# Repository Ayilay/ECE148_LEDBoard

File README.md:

# ECE148 LED Board

A PCB that arranges WS2812b individually addressable RGB LEDs in a rectangle underneath a Jetson Nano to give it a swank gaming-PC aesthetic.
Designed for [UCSD's ECE148 final project by Team 1, SP21](https://guitar.ucsd.edu/maeece148/index.php/2021SpringTeam1).

## PCB Overview

This PCB was hastily designed and is not my finest work, due to the time constraint we faced and the
fact that turnaround times for PCBs take a few days unless one pays a small fortune.

The PCB was designed in [KiCad](https://www.kicad.org/).

**Features:**
- STM32 F103C8T6 Microcontroller
- 10-pin SWD debug header
- JST-PH power connector with MIC5219 3V3 LDO Regulator
- Power LED
- Input voltage range from 3.7 V to 5V
- 16x WS2812b (aka Neopixels) arranged in a rectangle

**Absent Features**

I mention these not to roast myself (well kinda), but as a disclaimer to those looking at my design 
as reference for theirs. As I mentioned, I was on a time crunch so I couldn't afford the time to make this
a good-quality PCB. The following features should be included in a good design:
- Reset Pushbutton
- Generic I/O Breakouts
- Generic Button/LED for testing
- Testpoints for signals/power

## Firmware Overview

I used Michael Tien's STM32 code for [driving WS2812B LEDs using SPI over DMA](https://michaeltien8901.github.io/stm32/2018/07/19/Using-STM32-SPI-For-LED-STRIP.html)

Porting his code was easy. I created a new STM32CubeMX project for an STM32F103C8T6 microcontroller,
enabled the SPI1 peripheral, added a DMA channel for it, and set the clock as he described.

Then I automatically generated the code, and copied over Tien's helper functions from his `main.c` file,
and it worked like a charm. His functions are very straightforward to use, so thanks!

## Programming the board

(TODO Pictures)

I dislike using clunky IDEs unless I absolutely have to (i.e. for large projects). So I setup my CubeMX
project to use a Makefile, and use `make` to compile the code. Then I use my STLink V3-SET debug adapter
to flash the code, though any ST-Link probe that has a mini 10-pin cable will do. A quick guide on how
I flash STM32 code is on my [CubeProgrammer TechNotes](https://github.com/Ayilay/dotfiles/blob/master/techNotes/CubeProgrammer.md)

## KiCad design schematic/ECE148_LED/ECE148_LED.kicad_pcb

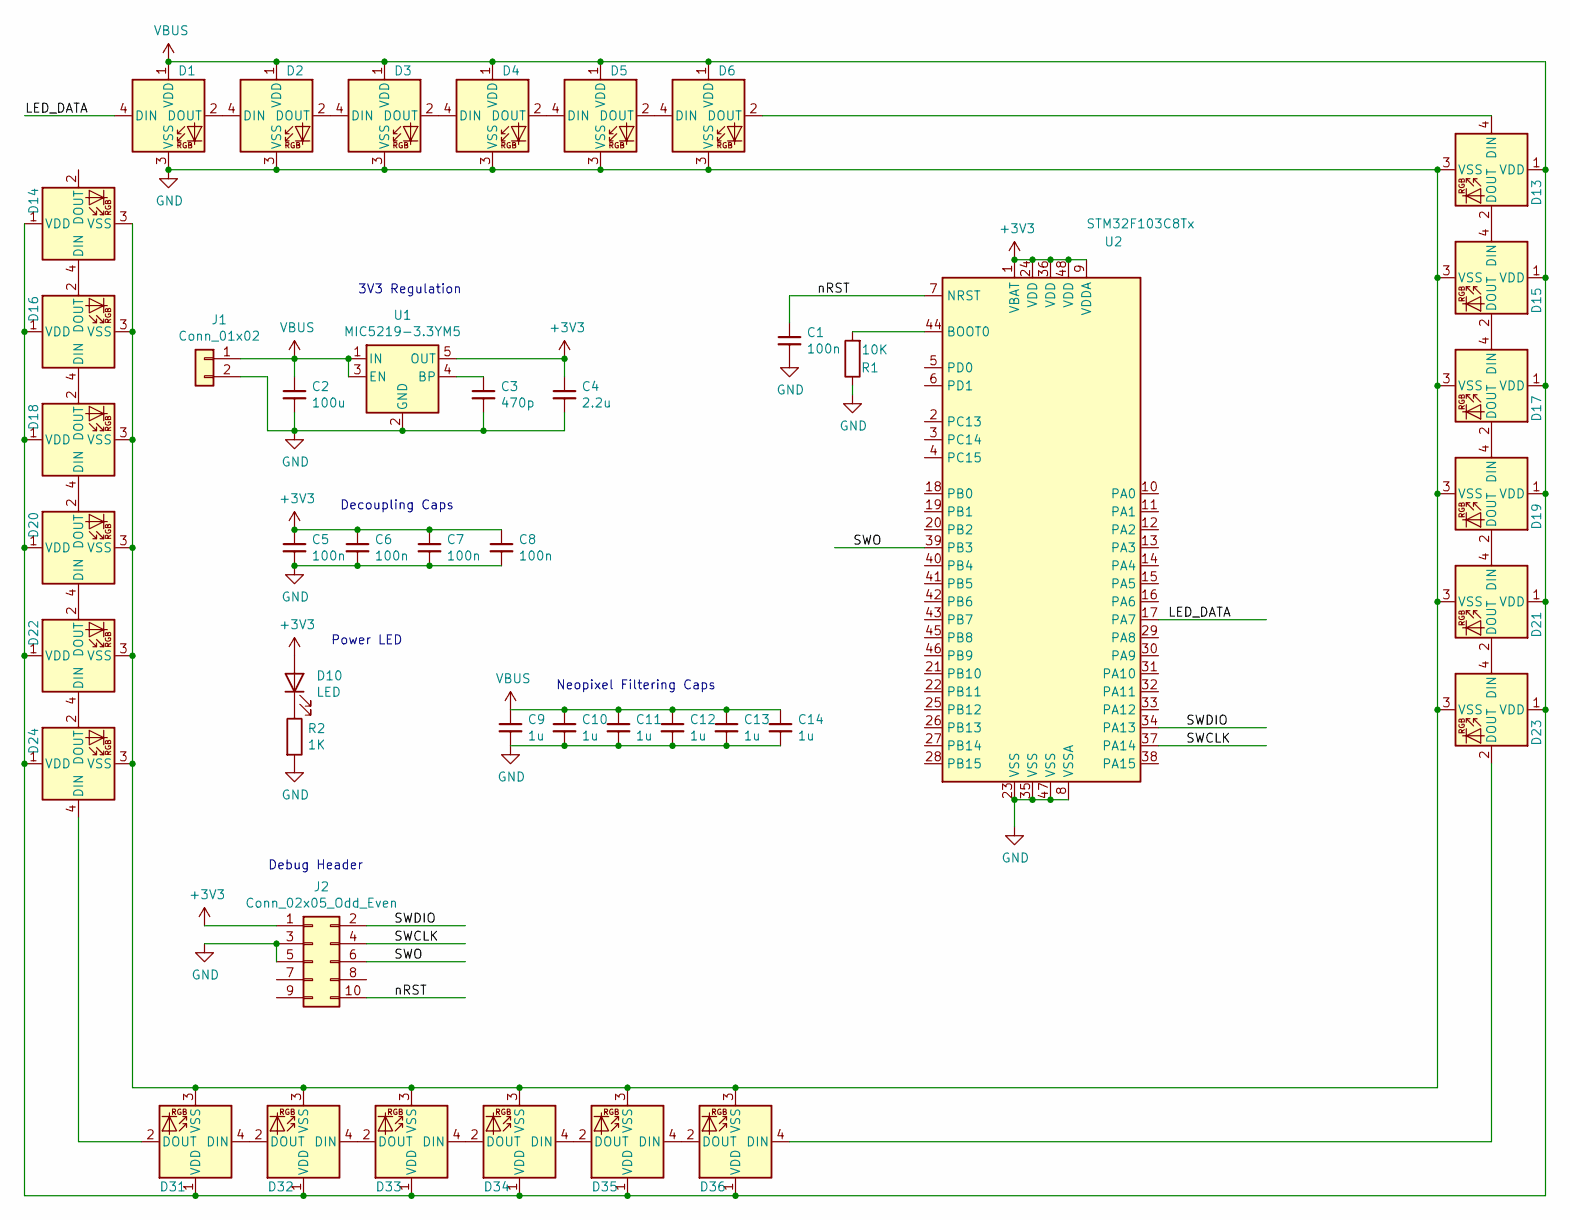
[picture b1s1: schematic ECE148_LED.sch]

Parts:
C1, C5, C6, C7, C8: 100n; C_0603_1608Metric
C2: 100u; CP_Radial_D5.0mm_P2.00mm
C3: 470p; C_0603_1608Metric
C4: 2.2u; C_0603_1608Metric
C9, C10, C11, C12, C13, C14: 1u; C_0603_1608Metric
D1, D2, D3, D4, D5, D6, D13, D14, D15, D16, D17, D18, D19, D20, D21, D22, D23, D24, D31, D32, D33, D34, D35, D36: WS2812B; LED_WS2812B_PLCC4_5.0x5.0mm_P3.2mm
D10: LED; LED_0805_2012Metric
J1: Conn_01x02; JST_PH_B2B-PH-K_1x02_P2.00mm_Vertical
J2: Conn_02x05_Odd_Even; PinHeader_2x05_P1.27mm_Vertical_SMD
R1: 10K; R_0603_1608Metric
R2: 1K; R_0603_1608Metric
U1: MIC5219-3.3YM5; SOT-23-5
U2: STM32F103C8Tx; LQFP-48_7x7mm_P0.5mm

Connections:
+3V3: C4.1, C5.1, C6.1, C7.1, C8.1, D10.2 (A), J2.1, U1.5 (OUT), U2.1 (VBAT), U2.9 (VDDA), U2.24 (VDD), U2.36 (VDD), U2.48 (VDD)
/LED_DATA: D1.4 (DIN), U2.17 (PA7)
/SWCLK: J2.4, U2.37 (PA14)
/SWDIO: J2.2, U2.34 (PA13)
/SWO: J2.6, U2.39 (PB3)
/nRST: C1.1, J2.10, U2.7 (NRST)
GND: C1.2, C2.2, C3.2, C4.2, C5.2, C6.2, C7.2, C8.2, C9.2, C10.2, C11.2, C12.2, C13.2, C14.2, D1.3 (VSS), D2.3 (VSS), D3.3 (VSS), D4.3 (VSS), D5.3 (VSS), D6.3 (VSS), D13.3 (VSS), D14.3 (VSS), D15.3 (VSS), D16.3 (VSS), D17.3 (VSS), D18.3 (VSS), D19.3 (VSS), D20.3 (VSS), D21.3 (VSS), D22.3 (VSS), D23.3 (VSS), D24.3 (VSS), D31.3 (VSS), D32.3 (VSS), D33.3 (VSS), D34.3 (VSS), D35.3 (VSS), D36.3 (VSS), J1.2, J2.3, J2.5, R1.1, R2.2, U1.2 (GND), U2.8 (VSSA), U2.23 (VSS), U2.35 (VSS), U2.47 (VSS)
unnamed: C3.1, U1.4 (BP)
unnamed: D1.2 (DOUT), D2.4 (DIN)
unnamed: D2.2 (DOUT), D3.4 (DIN)
unnamed: D3.2 (DOUT), D4.4 (DIN)
unnamed: D4.2 (DOUT), D5.4 (DIN)
unnamed: D5.2 (DOUT), D6.4 (DIN)
unnamed: D10.1 (K), R2.1
unnamed: D13.2 (DOUT), D15.4 (DIN)
unnamed: D6.2 (DOUT), D13.4 (DIN)
unnamed: D14.4 (DIN), D16.2 (DOUT)
unnamed: D15.2 (DOUT), D17.4 (DIN)
unnamed: D16.4 (DIN), D18.2 (DOUT)
unnamed: D17.2 (DOUT), D19.4 (DIN)
unnamed: D18.4 (DIN), D20.2 (DOUT)
unnamed: D19.2 (DOUT), D21.4 (DIN)
unnamed: D20.4 (DIN), D22.2 (DOUT)
unnamed: D21.2 (DOUT), D23.4 (DIN)
unnamed: D22.4 (DIN), D24.2 (DOUT)
unnamed: D23.2 (DOUT), D36.4 (DIN)
unnamed: D24.4 (DIN), D31.2 (DOUT)
unnamed: D31.4 (DIN), D32.2 (DOUT)
unnamed: D32.4 (DIN), D33.2 (DOUT)
unnamed: D33.4 (DIN), D34.2 (DOUT)
unnamed: D34.4 (DIN), D35.2 (DOUT)
unnamed: D35.4 (DIN), D36.2 (DOUT)
unnamed: R1.2, U2.44 (BOOT0)
VBUS: C2.1, C9.1, C10.1, C11.1, C12.1, C13.1, C14.1, D1.1 (VDD), D2.1 (VDD), D3.1 (VDD), D4.1 (VDD), D5.1 (VDD), D6.1 (VDD), D13.1 (VDD), D14.1 (VDD), D15.1 (VDD), D16.1 (VDD), D17.1 (VDD), D18.1 (VDD), D19.1 (VDD), D20.1 (VDD), D21.1 (VDD), D22.1 (VDD), D23.1 (VDD), D24.1 (VDD), D31.1 (VDD), D32.1 (VDD), D33.1 (VDD), D34.1 (VDD), D35.1 (VDD), D36.1 (VDD), J1.1, U1.1 (IN), U1.3 (EN)

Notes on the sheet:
Decoupling Caps
3V3 Regulation
Power LED
Debug Header
Neopixel Filtering Caps

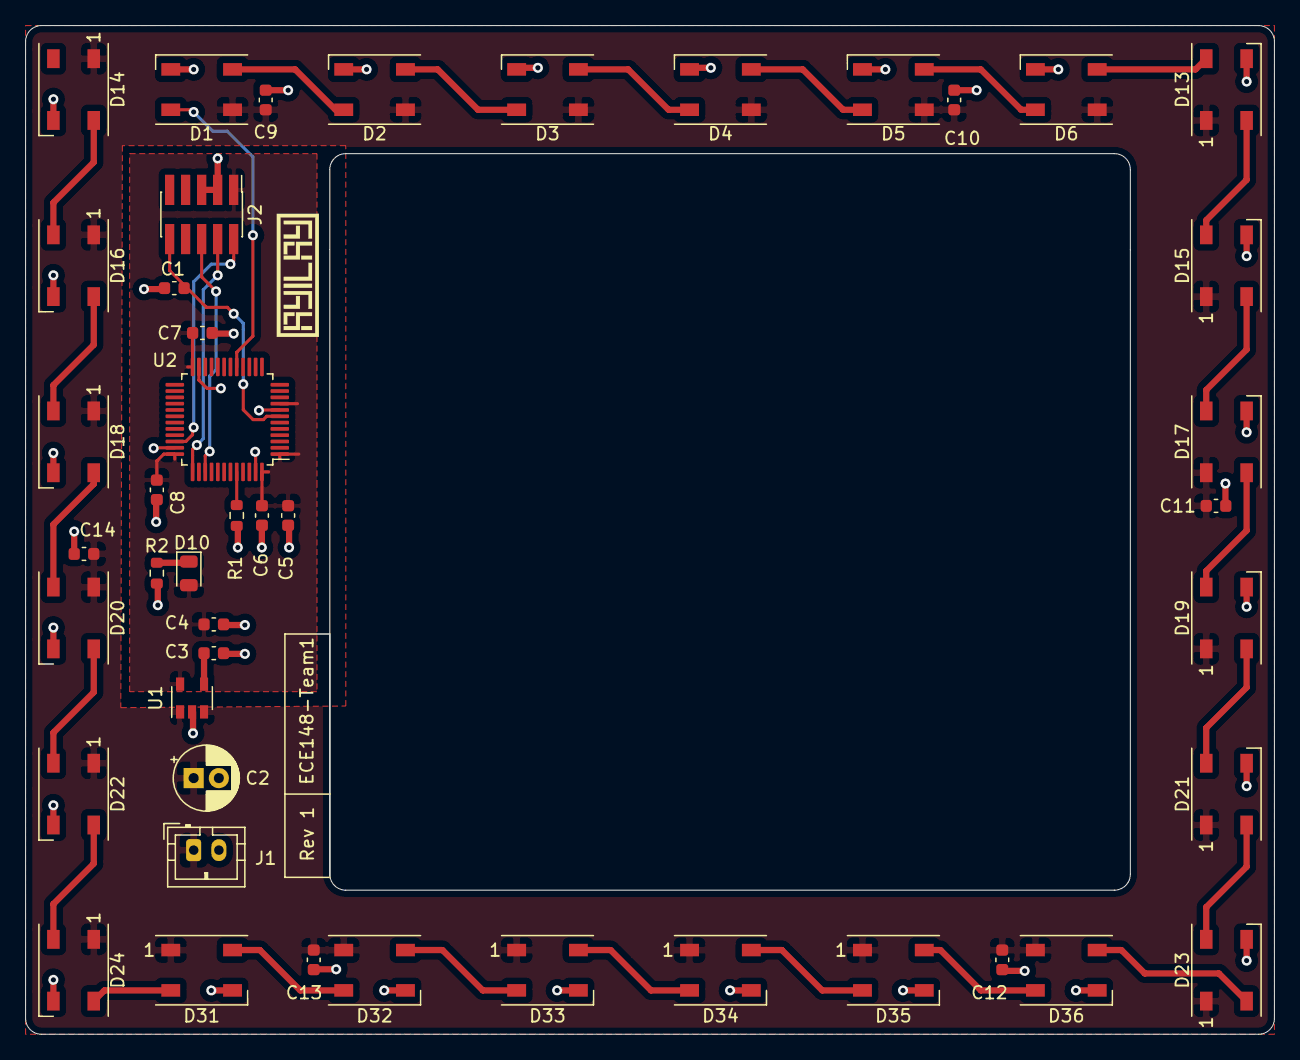
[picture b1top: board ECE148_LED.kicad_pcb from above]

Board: 2 copper layers, 99.1 x 80.0 mm, 45 parts (0 on the bottom side), 34 nets.

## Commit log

2021-06-03 Added picture of PCB
2021-06-03 Added schematic files
2021-06-03 Added KiCad credits to README
2021-06-04 Fixed dumb typo, and new compiled binaries
2021-06-08 Added GIF of LED Board working
2021-06-08 Made LED Board GIF larger
2021-06-08 Added Team1 Wiki link
2021-06-08 Updated LED pattern to be 4 chasing LEDs around the ring
2021-06-08 Added 3rd LED Pattern, Linear Chasing
2021-06-09 Added gif of LEDBoard mounted on car
2021-06-09 Fix gif of car ledboard
2021-06-09 Resized gifs again
2021-06-09 Enhanced 3rd Chaser Pattern
